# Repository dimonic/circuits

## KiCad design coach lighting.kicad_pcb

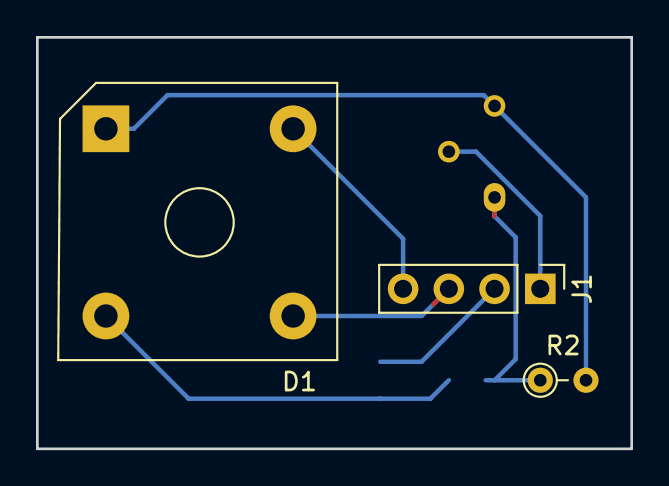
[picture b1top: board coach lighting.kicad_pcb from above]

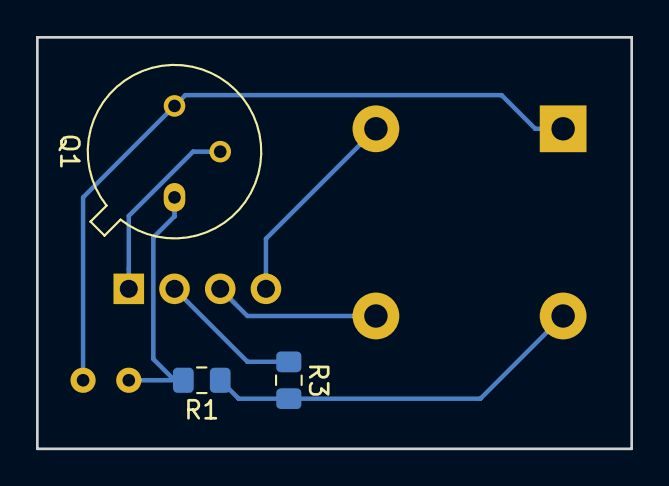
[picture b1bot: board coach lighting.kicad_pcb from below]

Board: 2 copper layers, 33.0 x 22.9 mm, 6 parts (3 on the bottom side), 7 nets.

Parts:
D1: D_Bridge_+-AA; Diode_Bridge_Vishay_KBPC6
J1: Conn_01x04_Male; PinHeader_1x04_P2.54mm_Vertical
Q1: Q_NPN_BCE; TO-39-3
R1, R3: R_Small_US; R_0805_2012Metric_Pad1.15x1.40mm_HandSolder
R2: R_PHOTO; R_Axial_DIN0204_L3.6mm_D1.6mm_P2.54mm_Vertical

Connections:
unnamed: D1.1, Q1.3, R2.2
unnamed: D1.2, R1.1, R3.2
unnamed: D1.3, J1.3
unnamed: D1.4, J1.4
unnamed: J1.1, Q1.2
unnamed: J1.2, R3.1
unnamed: Q1.1, R1.2, R2.1

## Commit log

2021-08-30 initial schema
